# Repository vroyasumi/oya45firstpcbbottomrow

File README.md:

# oya45firstpcbbottomrow
 bottom row

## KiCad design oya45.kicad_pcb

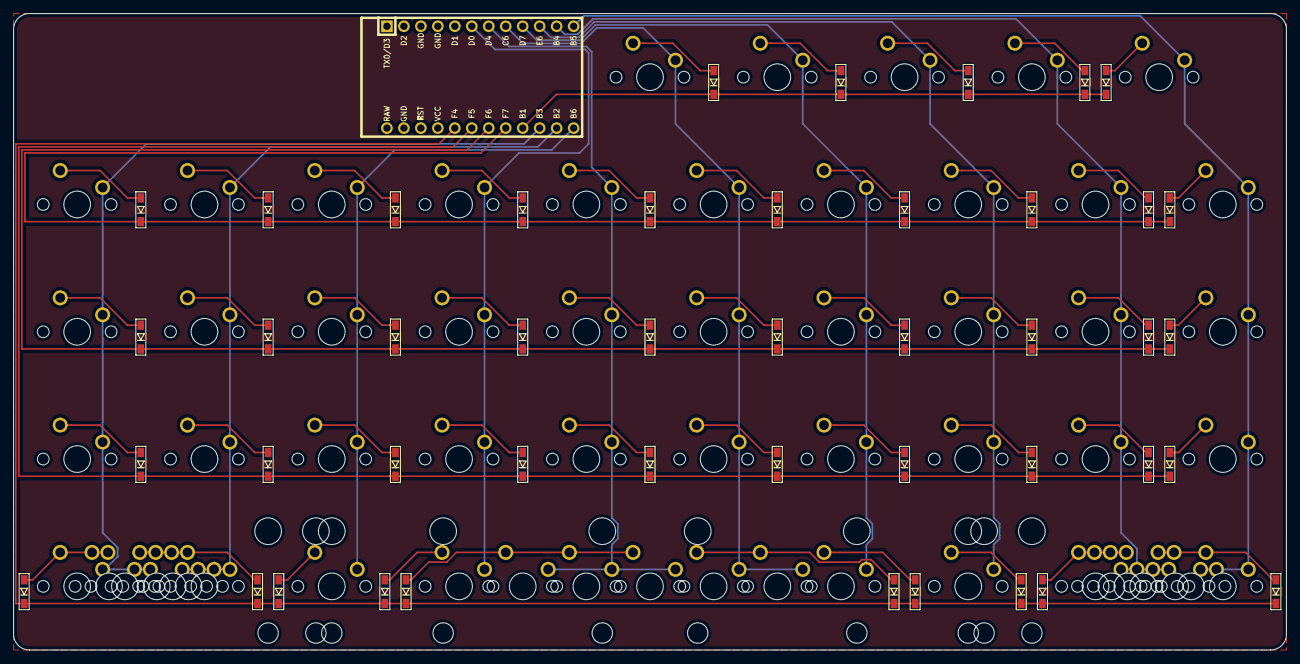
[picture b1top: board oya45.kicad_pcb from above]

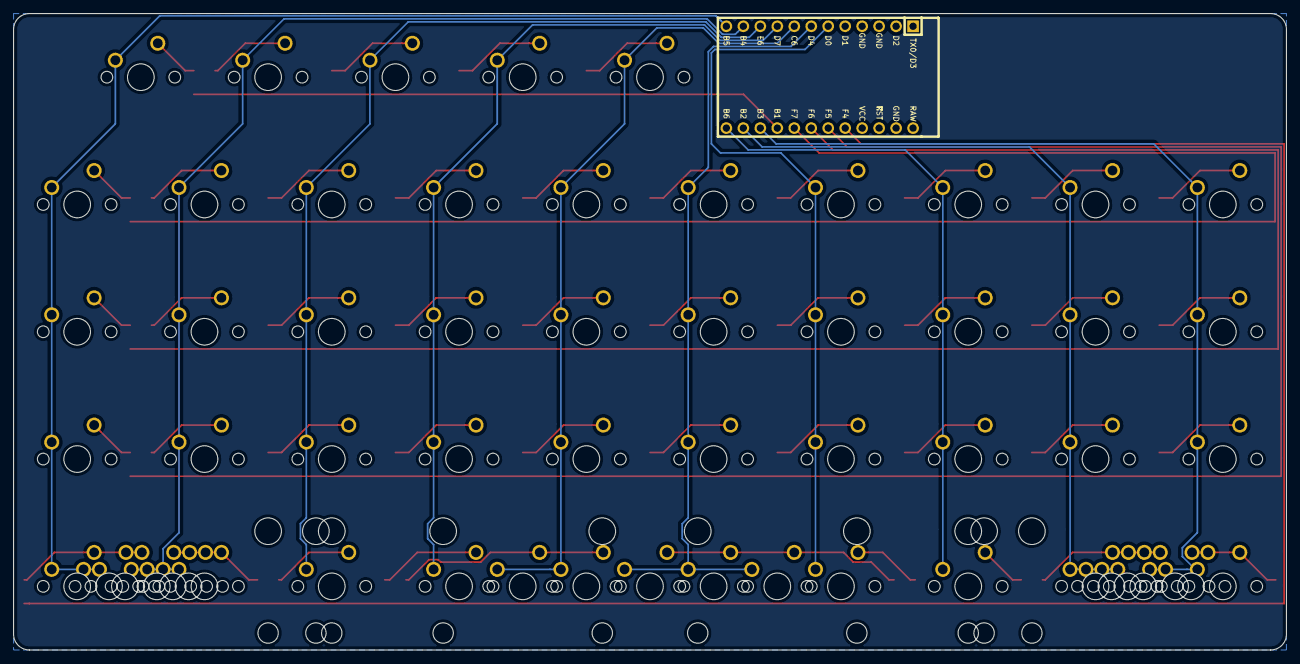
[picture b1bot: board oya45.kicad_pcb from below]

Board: 2 copper layers, 190.5 x 95.2 mm, 106 parts (61 on the bottom side), 60 nets.

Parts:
D1, D2, D3, D4, D5, D6, D7, D8, D9, D10, D11, D12, D13, D14, D15, D16, D17, D18, D19, D20, D21, D22, D23, D24, D25, D26, D27, D28, D29, D30, D31, D32, D33, D34, D35, D36, D37, D38, D39, D40, D41, D42, D43, D44, D45: D_Small; D3_SMD_v2
MX1, MX2, MX3, MX4, MX5, MX6, MX7, MX8, MX9, MX10, MX11, MX12, MX13, MX14, MX15, MX16, MX17, MX18, MX19, MX20, MX21, MX22, MX23, MX24, MX25, MX26, MX27, MX28, MX29, MX30, MX31, MX32, MX33, MX34, MX35, MX36, MX37, MX38, MX39, MX40, MX41, MX42, MX43, MX44, MX45: MX-NoLED; MXOnly-1U-NoLED
MX46: MX-NoLED; MXOnly-6U-Centered-ReversedStabilizers-NoLED
MX47, MX48: MX-NoLED; MXOnly-2U-ReversedStabilizers-NoLED
MX49: MX-NoLED; MXOnly-6.25U-ReversedStabilizers-NoSwitch
MX50: MX-NoLED; MXOnly-7U-ReversedStabilizers-NoSwitch
MX51, MX52, MX53, MX57, MX58, MX59: MX-NoLED; MXOnly-1.25U-NoLED
MX54, MX55, MX60, MX61: MX-NoLED; MXOnly-1.5U-NoLED
U1: ProMicro; ArduinoProMicro

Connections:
unnamed: D1.2, MX1.2
unnamed: D2.2, MX2.2
unnamed: D3.2, MX3.2
unnamed: D4.2, MX4.2
unnamed: D5.2, MX5.2
unnamed: D6.2, MX6.2
unnamed: D7.2, MX7.2
unnamed: D8.2, MX8.2
unnamed: D9.2, MX9.2
unnamed: D10.2, MX10.2
unnamed: D11.2, MX11.2
unnamed: D12.2, MX12.2
unnamed: D13.2, MX13.2
unnamed: D14.2, MX14.2
unnamed: D15.2, MX15.2
unnamed: D16.2, MX16.2
unnamed: D17.2, MX17.2
unnamed: D18.2, MX18.2
unnamed: D19.2, MX19.2
unnamed: D20.2, MX20.2
unnamed: D21.2, MX21.2
unnamed: D22.2, MX22.2
unnamed: D23.2, MX23.2
unnamed: D24.2, MX24.2
unnamed: D25.2, MX25.2
unnamed: D26.2, MX26.2
unnamed: D27.2, MX27.2
unnamed: D28.2, MX28.2
unnamed: D29.2, MX29.2
unnamed: D30.2, MX30.2
unnamed: D31.2, MX31.2, MX53.2, MX55.2
unnamed: D32.2, MX32.2, MX51.2, MX52.2, MX54.2
unnamed: D33.2, MX33.2
unnamed: D34.2, MX34.2
unnamed: D35.2, MX35.2, MX46.2, MX47.2
unnamed: D36.2, MX36.2, MX48.2
unnamed: D37.2, MX37.2
unnamed: D38.2, MX38.2
unnamed: D39.2, MX39.2, MX57.2, MX58.2, MX60.2
unnamed: D40.2, MX40.2, MX59.2, MX61.2
unnamed: D41.2, MX41.2
unnamed: D42.2, MX42.2
unnamed: D43.2, MX43.2
unnamed: D44.2, MX44.2
unnamed: D45.2, MX45.2
col0: MX1.1, MX11.1, MX21.1, MX31.1, MX53.1, MX55.1, U1.15
col1: MX2.1, MX12.1, MX22.1, MX32.1, MX51.1, MX52.1, MX54.1, U1.14
col2: MX3.1, MX13.1, MX23.1, MX33.1, U1.13
col3: MX4.1, MX14.1, MX24.1, MX34.1, U1.6
col4: MX5.1, MX15.1, MX25.1, MX35.1, MX46.1, MX47.1, U1.7
col5: MX6.1, MX16.1, MX26.1, MX36.1, MX41.1, MX48.1, U1.8
col6: MX7.1, MX17.1, MX27.1, MX37.1, MX42.1, U1.9
col7: MX8.1, MX18.1, MX28.1, MX38.1, MX43.1, U1.10
col8: MX9.1, MX19.1, MX29.1, MX39.1, MX44.1, MX57.1, MX58.1, MX60.1, U1.11
col9: MX10.1, MX20.1, MX30.1, MX40.1, MX45.1, MX59.1, MX61.1, U1.12
row0: D41.1, D42.1, D43.1, D44.1, D45.1, U1.16
row1: D1.1, D2.1, D3.1, D4.1, D5.1, D6.1, D7.1, D8.1, D9.1, D10.1, U1.17
row2: D11.1, D12.1, D13.1, D14.1, D15.1, D16.1, D17.1, D18.1, D19.1, D20.1, U1.18
row3: D21.1, D22.1, D23.1, D24.1, D25.1, D26.1, D27.1, D28.1, D29.1, D30.1, U1.19
row4: D31.1, D32.1, D33.1, D34.1, D35.1, D36.1, D37.1, D38.1, D39.1, D40.1, U1.20

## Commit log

2021-09-02 duplicate files
2021-09-02 schematics update
    added bottom row schematics
2021-09-02 fixed schematic
2021-09-02 finish schematics
2021-09-02 added bottom row footprints
2021-09-02 fixed diodes
2021-09-02 finished pcb
2021-09-02 finished pcb and gerbers
2021-09-03 final
    finalized bottom row and pcb
2021-09-03 added callmevroyasumi soldermask
2021-09-03 final pcb with soldermask gerbers
2021-09-03 added callmevroyasumi both sides
2021-09-04 final
    rerouted tracks and added gerbers
2021-09-04 cmiyglvroyasumi footprint
    refreshed cmiygl footprint
2021-09-04 final
    added cmiyglvroyasumi and gerbers
2021-09-04 cleaned up switch position and tracks, and added gerbers
2021-09-06 added ground fill
2021-09-07 added gerbers
